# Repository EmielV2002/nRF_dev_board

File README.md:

# nRF dev board

A development board using the nRF53 and nPM1100 chip.

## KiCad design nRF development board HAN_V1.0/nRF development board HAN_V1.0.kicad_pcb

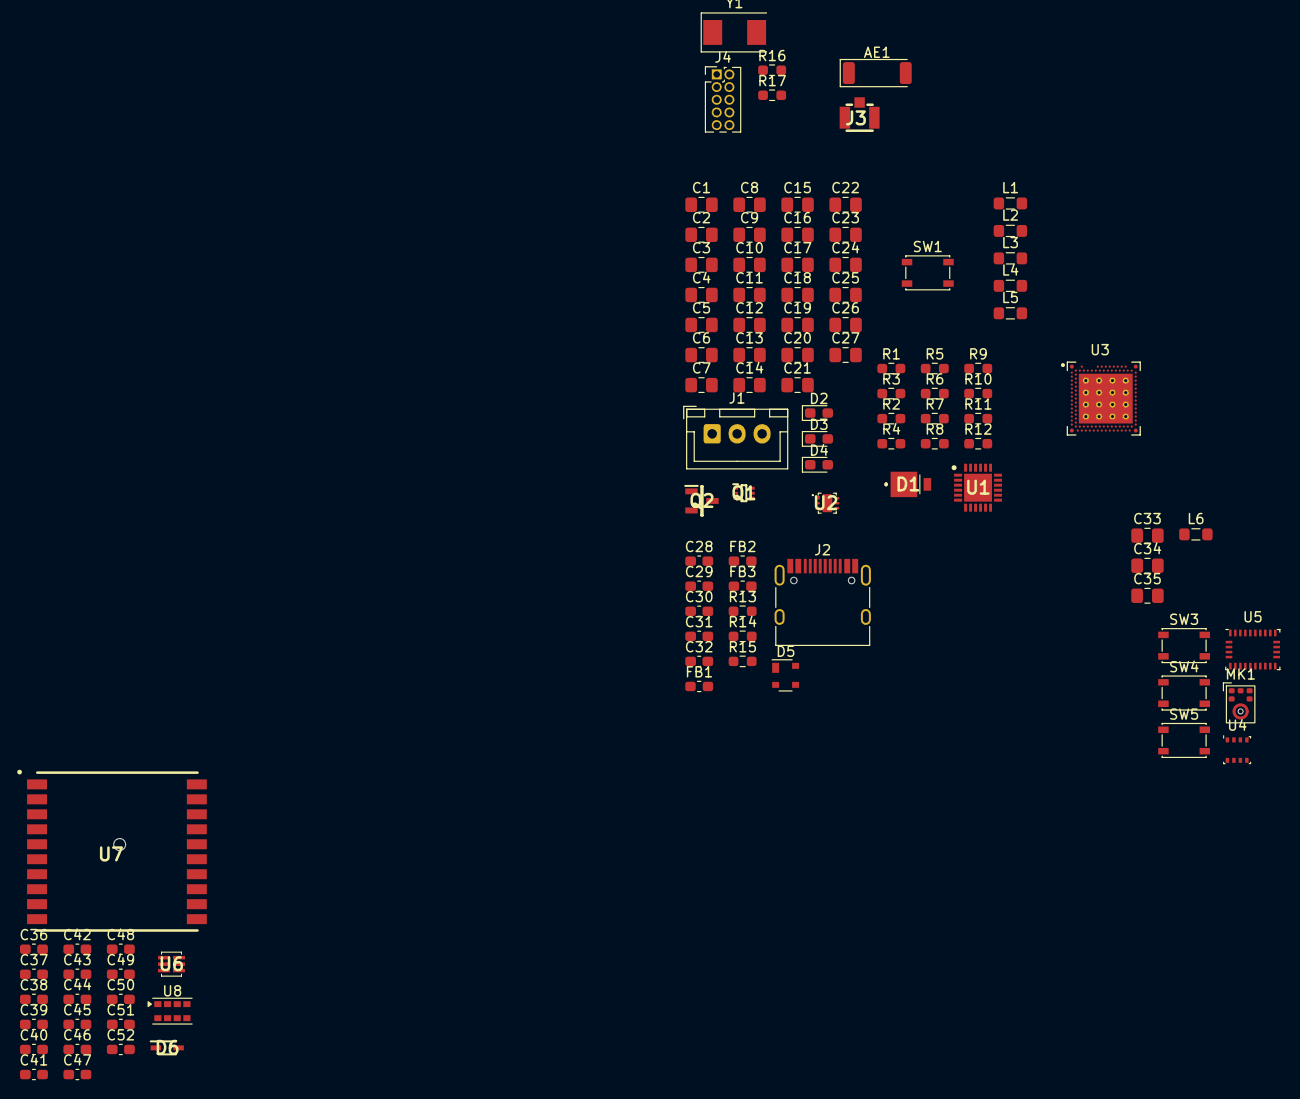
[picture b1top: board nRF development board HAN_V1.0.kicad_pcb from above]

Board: 4 copper layers, 105 parts (0 on the bottom side), 58 nets.

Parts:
AE1: Antenna; Johanson_2450AT43F0100
C1, C22: 2.2uF; C_0805_2012Metric_Pad1.18x1.45mm_HandSolder
C2, C3, C6, C7: 10uF; C_0805_2012Metric_Pad1.18x1.45mm_HandSolder
C4, C23, C24, C25: 4.7uF; C_0805_2012Metric_Pad1.18x1.45mm_HandSolder
C5: 15pF; C_0805_2012Metric_Pad1.18x1.45mm_HandSolder
C8, C13, C14, C20, C21, C27: 1uF; C_0805_2012Metric_Pad1.18x1.45mm_HandSolder
C9, C10, C11, C12, C16, C17, C18, C19, C26: 100nF; C_0805_2012Metric_Pad1.18x1.45mm_HandSolder
C15: 2.2nF; C_0805_2012Metric_Pad1.18x1.45mm_HandSolder
C28, C30, C37, C43, C45: 1.0uF; C_0603_1608Metric_Pad1.08x0.95mm_HandSolder
C29, C31, C36, C38, C39, C42, C46, C47, C48, C49, C50, C51, C52: 100nF; C_0603_1608Metric_Pad1.08x0.95mm_HandSolder
C32: 100nF 2kV; C_0603_1608Metric_Pad1.08x0.95mm_HandSolder
C33: 1.2pF; C_0805_2012Metric_Pad1.18x1.45mm_HandSolder
C34: DNP; C_0805_2012Metric_Pad1.18x1.45mm_HandSolder
C35: 0.7pF; C_0805_2012Metric_Pad1.18x1.45mm_HandSolder
C40, C41: 22pF; C_0603_1608Metric_Pad1.08x0.95mm_HandSolder
C44: 220pF; C_0603_1608Metric_Pad1.08x0.95mm_HandSolder
D1: MBRM110ET3G; MBRM110LT1G
D2, D4: RED; LED_0603_1608Metric_Pad1.05x0.95mm_HandSolder
D3: GREEN; LED_0603_1608Metric_Pad1.05x0.95mm_HandSolder
D5: PRTR5V0U2X; SOT-143
D6: CUS520,H3F; SOD2513X115N
FB1, FB2, FB3: 120R 0.55A; L_0603_1608Metric_Pad1.05x0.95mm_HandSolder
J1: Conn_01x03_Pin; JST_XH_B3B-XH-A_1x03_P2.50mm_Vertical
J2: USB_C_Receptacle_USB2.0; USB_C_Receptacle_HRO_TYPE-C-31-M-12
J3: U.FL-R-SMT-1_10_
J4: Conn_02x05_Top_Bottom; PinHeader_2x05_P1.27mm_Vertical
L1: 4.7uH; L_0805_2012Metric_Pad1.05x1.20mm_HandSolder
L2: 2.2uH; L_0805_2012Metric_Pad1.05x1.20mm_HandSolder
L3, L4, L5: 10uH; L_0805_2012Metric_Pad1.05x1.20mm_HandSolder
L6: 2.2nH; L_0805_2012Metric_Pad1.05x1.20mm_HandSolder
MK1: SPH0645LM4H; Knowles_SPH0645LM4H-6_3.5x2.65mm
Q1: DMC2400UV; SOTFL50P162X60-6N
Q2: FDV303N; SOT96P237X111-3N
R1: 375k; R_0603_1608Metric_Pad0.98x0.95mm_HandSolder
R2: 120k; R_0603_1608Metric_Pad0.98x0.95mm_HandSolder
R3, R5, R15: 10k; R_0603_1608Metric_Pad0.98x0.95mm_HandSolder
R4: 1k; R_0603_1608Metric_Pad0.98x0.95mm_HandSolder
R6: 2.2k; R_0603_1608Metric_Pad0.98x0.95mm_HandSolder
R7: 150; R_0603_1608Metric_Pad0.98x0.95mm_HandSolder
R8, R9, R10, R12: 1M; R_0603_1608Metric_Pad0.98x0.95mm_HandSolder
R11: 220k; R_0603_1608Metric_Pad0.98x0.95mm_HandSolder
R13, R14: 5.1k; R_0603_1608Metric_Pad0.98x0.95mm_HandSolder
R16, R17: 27; R_0603_1608Metric_Pad0.98x0.95mm_HandSolder
SW1, SW3, SW4, SW5: SW_Push; SW_SPST_PTS810
U1: NPM1100-QDAA-R; QFN50P400X400X90-25N-D
U2: XC9236F08CER-G; XC9236F08CERG
U3: NRF5340-QKAA-R7; XCVR_NRF5340-QKAA-R7
U4: BME280; Bosch_LGA-8_2.5x2.5mm_P0.65mm_ClockwisePinNumbering
U5: BNO055; LGA-28_5.2x3.8mm_P0.5mm
U6: TSL25911FN
U7: FGPMMOPA6H
U8: APDS-9960; Avago_APDS-9960
Y1: 32mHz; Crystal_SMD_0603-2Pin_6.0x3.5mm

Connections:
+3V0: C7.2, C9.2, C10.2, C11.2, C12.2, C13.2, C16.2, C17.2, C18.2, C19.2, C20.2, C22.2, J4.1, L2.1, L5.1, R7.1, U1.1 (VOUTB), U3.A19 (VDD1), U3.AC1 (VDD), U3.AG1 (VDD), U3.AJ31 (VDD), U3.AL3 (VDD), U3.AL7 (VDD), U3.AL11 (VDD), U3.AL17 (VDD), U3.AL25 (VDD), U3.B8 (VDD2), U3.B28 (VDD), U3.C1 (VDD), U3.E31 (VDD), U3.L1 (VDD3), U3.N31 (VDD), U3.U1 (VDD)
+3V3: C5.2, C6.2, C37.1, C38.1, C42.1, C43.1, C44.1, C45.1, C46.1, C47.1, L1.2, MK1.5 (VDD), R1.1, U4.6 (VDDIO), U4.8 (VDD), U5.3 (VDD), U5.4 (~BOOT_LOAD_PIN), U5.28 (VDDIO), U6.5 (VDD), U7.1 (VCC), U8.5 (LED_A), U8.8 (VCC)
+5V: C3.2, C23.2, D1.2 (A), D2.2 (A), D3.2 (A), R6.1, U1.2 (VOUTBSET1), U1.3 (VOUTBSET0), U1.16 (VSYS), U3.E1 (VDDH)
+BATT: C8.2, J1.1, Q1.1 (S1), R5.2, R9.2, U1.15 (VBAT)
/Actuators/I2C_SCL: U5.19 (COM1), U6.1 (SCL), U8.7 (SCL)
/Actuators/I2C_SDA: U5.20 (COM0), U6.6 (SDA), U8.1 (SDA)
/MCU/BAT_MON: R10.1, R11.2
/MCU/BAT_MON_EN: Q1.5 (G2), R8.2
/MCU/CHG: D3.1 (K), U1.8 (CHG)
/MCU/D+: R17.2, U3.B2 (D+)
/MCU/D-: R16.2, U3.B4 (D-)
/MCU/ERR: D2.1 (K), U1.10 (ERR)
/MCU/LOW_BAT: Q2.1 (G), R12.2
/MCU/SW1: C48.1, SW3.1
/MCU/SW2: C49.1, SW4.1
/MCU/SW3: C50.1, SW5.1
/MCU/SWDCLK: J4.7, U3.W31 (SWDCLK)
/MCU/SWDIO: J4.6, U3.AA31 (SWDIO)
/MCU/USB_D+: D5.3 (I/O2), J2.A6 (D+), J2.B6 (D+), R17.1, U1.20 (D+)
/MCU/USB_D-: D5.2 (I/O1), J2.A7 (D-), J2.B7 (D-), R16.1, U1.19 (D-)
/MCU/~RESET: J4.10, U3.AC31 (~RESET)
/Power/NTC: J1.2, R3.1, U1.14 (NTC)
/Sensors/VBACKUP: D6.1 (K), U7.4 (VBACKUP)
/USB/CC1: J2.A5 (CC1), R14.1
/USB/CC2: J2.B5 (CC2), R13.1
/USB/GND: FB2.2, J2.A1 (GND), J2.A12 (GND), J2.B1 (GND), J2.B12 (GND)
/USB/SHIELD: C32.2, FB3.1, J2.S1 (SHIELD), R15.1
GNDD: C1.1, C2.1, C3.1, C4.1, C5.1, C6.1, C7.1, C8.1, C9.1, C10.1, C11.1, C12.1, C13.1, C14.1, C15.1, C16.1, C17.1, C18.1, C19.1, C20.1, C21.1, C22.1, C23.1, C24.1, C25.1, C26.1, C27.1, C28.2, C29.2, C30.2, C31.2, C32.1, C33.1, C34.1, C35.1, C36.2, C37.2, C38.2, C39.2, C40.2, C41.2, C42.2, C43.2, C44.2, C45.2, C46.2, C47.2, C48.2, C49.2, C50.2, C51.2, C52.2, D5.1 (GND), FB2.1, FB3.2, J1.3, J3.1, J3.2, J4.2, J4.3, MK1.3 (GND), Q1.4 (S2), Q2.2 (S), R2.2, R3.2, R4.2, R8.1, R11.1, R12.1, R13.2, R14.2, R15.2, SW1.2, SW3.2, SW4.2, SW5.2, U1.4 (AVSS), U1.7 (MODE), U1.9 (VTERMSET), U1.18 (NC_3), U1.23 (PVSS), U1.25 (EP), U2.2 (VSS_1), U2.5 (VSS_2), U2.7 (EP_1), U2.8 (EP_2), U2.9 (EP_3), U3.35 (VSS_PAD), U3.36 (VSS_PAD), U3.37 (VSS_PAD), U3.38 (VSS_PAD), U3.39 (VSS_PAD), U3.40 (VSS_PAD), U3.41 (VSS_PAD), U3.43 (VSS_PAD), U3.44 (VSS_PAD), U3.45 (VSS_PAD), U3.46 (VSS_PAD), U3.47 (VSS_PAD), U3.48 (VSS_PAD), U3.49 (VSS_PAD), U3.50 (VSS_PAD), U3.51 (VSS_PAD), U3.104 (VSS_PAD), U3.A25 (VSS), U3.B12 (VSS), U3.B26 (VSS), U3.G1 (VSS), U3.H2 (VSS), U3.J31 (VSS), U4.1 (GND), U4.7 (GND), U5.2 (GND), U5.10 (BL_IND), U5.15 (GNDIO), U5.16 (GNDIO), U5.18 (COM2), U5.25 (GNDIO), U6.3 (GND), U7.3 (GND_1), U7.8 (GND_2), U7.12 (GND_3), U7.19 (GND_4), U8.6 (GND)
unnamed: AE1.1 (A), C33.2, C34.2, J3.3, L6.1
unnamed: C4.2, D1.1 (K), U2.6 (VIN)
unnamed: D4.2 (A), R7.2
unnamed: D4.1 (K), Q2.3 (D)
unnamed: Q1.6 (D1), R10.2
unnamed: Q1.2 (G1), Q1.3 (D2), R9.1
unnamed: C2.2, U1.21 (DEC)
unnamed: R4.1, U1.12 (ICHG)
unnamed: R5.1, SW1.1, U1.11 (SHPHLD)
unnamed: L2.2, U1.22 (SW)
unnamed: L1.1, U2.1 (LX)
unnamed: R1.2, R2.1, U2.3 (VOUT(FB))
unnamed: L3.1, U3.A21 (DCC)
unnamed: L4.1, U3.B10 (DCCD)
unnamed: L5.2, U3.J1 (DCCH)
unnamed: C27.2, U3.A13 (DECA)
unnamed: C21.2, L4.2, U3.A15 (DECD)
unnamed: C26.2, U3.A23 (DECN)
unnamed: C14.2, C15.2, L3.2, U3.A27 (DECR), U3.G31 (DECRF)
unnamed: C25.2, U3.B6 (DECUSB)
unnamed: C24.2, R6.2, U3.A5 (VBUS)
unnamed: C35.2, L6.2, U3.L31 (ANT)
unnamed: U3.C31 (XC1), Y1.1
unnamed: U3.B30 (XC2), Y1.2
unnamed: C39.1, U5.9 (CAP)
unnamed: C41.1, U5.27 (XIN32)
unnamed: C40.1, U5.26 (XOUT32)
unnamed: U8.3 (LDR), U8.4 (LED_K)
VBUS: C1.2, C29.1, FB1.2, U1.17 (VBUS)
VDC: C28.1, C30.1, C31.1, D5.4 (VCC), FB1.1, J2.A4 (VBUS), J2.A9 (VBUS), J2.B4 (VBUS), J2.B9 (VBUS)

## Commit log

2024-01-15 Add README and license
2024-01-15 Create LICENSE
2024-01-27 Backups
2024-02-05 Updated schematic
2024-04-26 QOL update
2024-08-15 Updated PCB
